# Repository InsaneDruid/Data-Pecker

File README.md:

# The Data Pecker - a DB High-Res clone
The Data Pecker is a 100% compatible clone of the DB High-Res graphics board for PET/CBM 8000 series computers from 1982.
It implements all the features, with the option to build a 62256-based RAM-board instead of the original one using eight 6116.
Most of the components are readily available. Chips not available from Mouser or Digikey can still be purchased from a variety of sources in China. 

[Schematic](https://github.com/InsaneDruid/Data-Pecker/blob/main/dph_mainboard/dph_mainboard.pdf "Schematic")  

[Bill of Materials](https://htmlpreview.github.io/?https://github.com/InsaneDruid/Data-Pecker/blob/main/dph_mainboard/bom/dph_mainboard_bom.html "Bill of Materials")

[Wire connections](https://github.com/InsaneDruid/Data-Pecker/blob/main/dph_mainboard/dph_mainboard_connections.pdf "Wire connections" )
## The original RAM Board
The is the true-to-the-original version of the RAM board containing eight 6116 SRAM ICs.

[Schematic](https://github.com/InsaneDruid/Data-Pecker/blob/main/dph_ram/dph_ram.pdf "Schematic")  

[Bill of Materials](https://htmlpreview.github.io/?https://github.com/InsaneDruid/Data-Pecker/blob/main/dph_ram/bom/dph_ram_bom.html "Bill of Materials")

## The simplified RAM Board
This version replaces the old SRAM chips with a more modern 62256.

[Schematic](https://github.com/InsaneDruid/Data-Pecker/blob/main/dph_ram_optimized/dph_ram_optimized.pdf "Schematic")  

[Bill of Materials](https://htmlpreview.github.io/?https://github.com/InsaneDruid/Data-Pecker/blob/main/dph_ram_optimized/bom/dph_ram_optimized_bom.html "Bill of Materials")

## The Firmware
There are several ways to get both the programmed 2332A	ROM and TBP18s030 PROM	
chips for the Low Speed Graphik. One is to use U29 and U11 from a original HSG. 
This works well and is especially interesting for those seeking to replace a broken original HSG pcb.

The other possibility is to program a 2532 EPROM replacing U29 and a 18S030 PROM (or compatible, like 82S123, 27S19, 6331, 74S288, 7603a)
replacing U11. The firmware needed for flashing can be found on the web. The 18S030 can also be replaced by a GAL.

## The License
This work is licensed under a Creative Commons Attribution-ShareAlike 4.0 International License.  
See https://creativecommons.org/licenses/by-sa/4.0/.

## The Credits
This work would not have been possible without the help from a bunch of amazing people from [VzEkC e. V. forums](https://forum.classic-computing.de/forum/ "forum.classic-computing.de"). Many thanks go out to:

* *Toast_r* - for providing reference images and ohming out the hidden traces

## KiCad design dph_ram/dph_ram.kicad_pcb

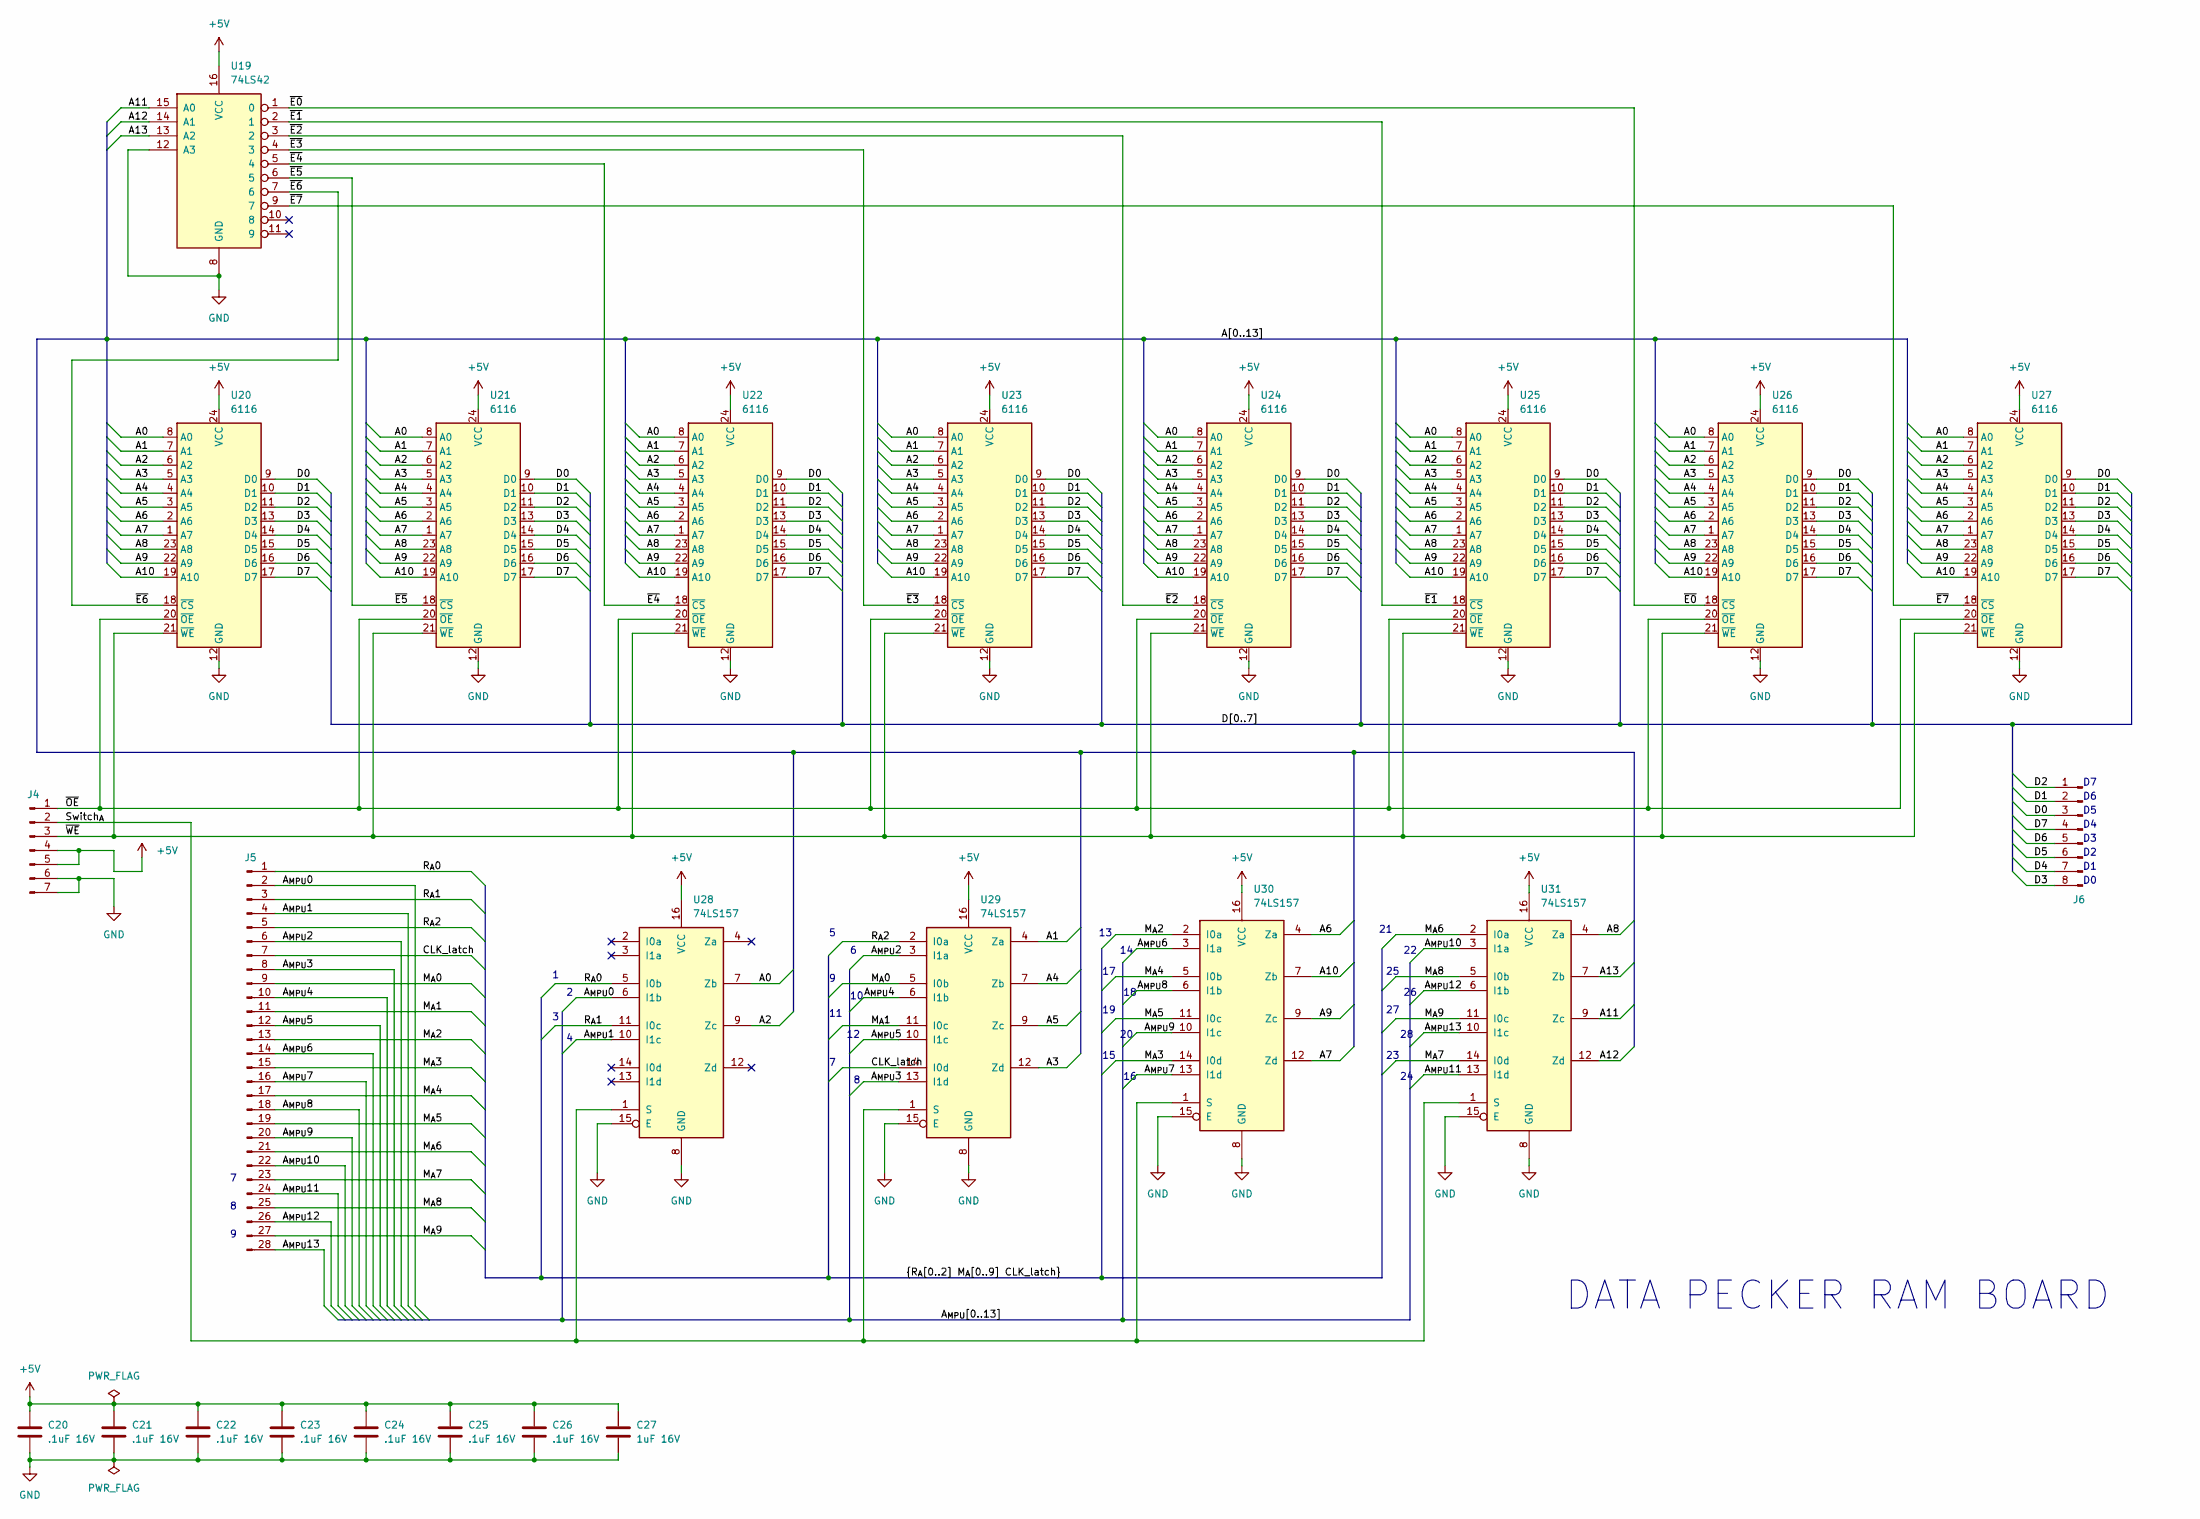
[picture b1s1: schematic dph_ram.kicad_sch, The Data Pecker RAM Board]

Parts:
C20, C21, C22, C23, C24, C25, C26: .1uF 16V; C_Disc_D3.0mm_W1.6mm_P2.50mm
C27: 1uF 16V; C_Disc_D4.3mm_W1.9mm_P5.08mm
J4: Conn_01x07_Pin; PinHeader_1x07_P2.54mm_Vertical
J5: Conn_01x28_Pin; PinHeader_1x28_P2.54mm_Vertical
J6: Conn_01x08_Pin; PinHeader_1x08_P2.54mm_Vertical
U19: 74LS42; DIP-16_W7.62mm_LongPads
U20, U21, U22, U23, U24, U25, U26, U27: 6116; DIP-24_W15.24mm_LongPads
U28, U29, U30, U31: 74LS157; DIP-16_W7.62mm_LongPads

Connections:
+5V: C20.1, C21.1, C22.1, C23.1, C24.1, C25.1, C26.1, C27.1, J4.4, J4.5, U19.16 (VCC), U20.24 (VCC), U21.24 (VCC), U22.24 (VCC), U23.24 (VCC), U24.24 (VCC), U25.24 (VCC), U26.24 (VCC), U27.24 (VCC), U28.16 (VCC), U29.16 (VCC), U30.16 (VCC), U31.16 (VCC)
/A0: U20.8 (A0), U21.8 (A0), U22.8 (A0), U23.8 (A0), U24.8 (A0), U25.8 (A0), U26.8 (A0), U27.8 (A0), U28.7 (Zb)
/A1: U20.7 (A1), U21.7 (A1), U22.7 (A1), U23.7 (A1), U24.7 (A1), U25.7 (A1), U26.7 (A1), U27.7 (A1), U29.4 (Za)
/A2: U20.6 (A2), U21.6 (A2), U22.6 (A2), U23.6 (A2), U24.6 (A2), U25.6 (A2), U26.6 (A2), U27.6 (A2), U28.9 (Zc)
/A3: U20.5 (A3), U21.5 (A3), U22.5 (A3), U23.5 (A3), U24.5 (A3), U25.5 (A3), U26.5 (A3), U27.5 (A3), U29.12 (Zd)
/A4: U20.4 (A4), U21.4 (A4), U22.4 (A4), U23.4 (A4), U24.4 (A4), U25.4 (A4), U26.4 (A4), U27.4 (A4), U29.7 (Zb)
/A5: U20.3 (A5), U21.3 (A5), U22.3 (A5), U23.3 (A5), U24.3 (A5), U25.3 (A5), U26.3 (A5), U27.3 (A5), U29.9 (Zc)
/A6: U20.2 (A6), U21.2 (A6), U22.2 (A6), U23.2 (A6), U24.2 (A6), U25.2 (A6), U26.2 (A6), U27.2 (A6), U30.4 (Za)
/A7: U20.1 (A7), U21.1 (A7), U22.1 (A7), U23.1 (A7), U24.1 (A7), U25.1 (A7), U26.1 (A7), U27.1 (A7), U30.12 (Zd)
/A8: U20.23 (A8), U21.23 (A8), U22.23 (A8), U23.23 (A8), U24.23 (A8), U25.23 (A8), U26.23 (A8), U27.23 (A8), U31.4 (Za)
/A9: U20.22 (A9), U21.22 (A9), U22.22 (A9), U23.22 (A9), U24.22 (A9), U25.22 (A9), U26.22 (A9), U27.22 (A9), U30.9 (Zc)
/A10: U20.19 (A10), U21.19 (A10), U22.19 (A10), U23.19 (A10), U24.19 (A10), U25.19 (A10), U26.19 (A10), U27.19 (A10), U30.7 (Zb)
/A11: U19.15 (A0), U31.9 (Zc)
/A12: U19.14 (A1), U31.12 (Zd)
/A13: U19.13 (A2), U31.7 (Zb)
/A_{MPU}0: J5.2, U28.6 (I1b)
/A_{MPU}1: J5.4, U28.10 (I1c)
/A_{MPU}2: J5.6, U29.3 (I1a)
/A_{MPU}3: J5.8, U29.13 (I1d)
/A_{MPU}4: J5.10, U29.6 (I1b)
/A_{MPU}5: J5.12, U29.10 (I1c)
/A_{MPU}6: J5.14, U30.3 (I1a)
/A_{MPU}7: J5.16, U30.13 (I1d)
/A_{MPU}8: J5.18, U30.6 (I1b)
/A_{MPU}9: J5.20, U30.10 (I1c)
/A_{MPU}10: J5.22, U31.3 (I1a)
/A_{MPU}11: J5.24, U31.13 (I1d)
/A_{MPU}12: J5.26, U31.6 (I1b)
/A_{MPU}13: J5.28, U31.10 (I1c)
/CLK_latch: J5.7, U29.14 (I0d)
/D0: J6.3, U20.9 (D0), U21.9 (D0), U22.9 (D0), U23.9 (D0), U24.9 (D0), U25.9 (D0), U26.9 (D0), U27.9 (D0)
/D1: J6.2, U20.10 (D1), U21.10 (D1), U22.10 (D1), U23.10 (D1), U24.10 (D1), U25.10 (D1), U26.10 (D1), U27.10 (D1)
/D2: J6.1, U20.11 (D2), U21.11 (D2), U22.11 (D2), U23.11 (D2), U24.11 (D2), U25.11 (D2), U26.11 (D2), U27.11 (D2)
/D3: J6.8, U20.13 (D3), U21.13 (D3), U22.13 (D3), U23.13 (D3), U24.13 (D3), U25.13 (D3), U26.13 (D3), U27.13 (D3)
/D4: J6.7, U20.14 (D4), U21.14 (D4), U22.14 (D4), U23.14 (D4), U24.14 (D4), U25.14 (D4), U26.14 (D4), U27.14 (D4)
/D5: J6.6, U20.15 (D5), U21.15 (D5), U22.15 (D5), U23.15 (D5), U24.15 (D5), U25.15 (D5), U26.15 (D5), U27.15 (D5)
/D6: J6.5, U20.16 (D6), U21.16 (D6), U22.16 (D6), U23.16 (D6), U24.16 (D6), U25.16 (D6), U26.16 (D6), U27.16 (D6)
/D7: J6.4, U20.17 (D7), U21.17 (D7), U22.17 (D7), U23.17 (D7), U24.17 (D7), U25.17 (D7), U26.17 (D7), U27.17 (D7)
/M_{A}0: J5.9, U29.5 (I0b)
/M_{A}1: J5.11, U29.11 (I0c)
/M_{A}2: J5.13, U30.2 (I0a)
/M_{A}3: J5.15, U30.14 (I0d)
/M_{A}4: J5.17, U30.5 (I0b)
/M_{A}5: J5.19, U30.11 (I0c)
/M_{A}6: J5.21, U31.2 (I0a)
/M_{A}7: J5.23, U31.14 (I0d)
/M_{A}8: J5.25, U31.5 (I0b)
/M_{A}9: J5.27, U31.11 (I0c)
/R_{A}0: J5.1, U28.5 (I0b)
/R_{A}1: J5.3, U28.11 (I0c)
/R_{A}2: J5.5, U29.2 (I0a)
/Switch_{A}: J4.2, U28.1 (S), U29.1 (S), U30.1 (S), U31.1 (S)
/~E0: U19.1 (0), U26.18 (~CS)
/~E1: U19.2 (1), U25.18 (~CS)
/~E2: U19.3 (2), U24.18 (~CS)
/~E3: U19.4 (3), U23.18 (~CS)
/~E4: U19.5 (4), U22.18 (~CS)
/~E5: U19.6 (5), U21.18 (~CS)
/~E6: U19.7 (6), U20.18 (~CS)
/~E7: U19.9 (7), U27.18 (~CS)
/~OE: J4.1, U20.20 (~OE), U21.20 (~OE), U22.20 (~OE), U23.20 (~OE), U24.20 (~OE), U25.20 (~OE), U26.20 (~OE), U27.20 (~OE)
/~WE: J4.3, U20.21 (~WE), U21.21 (~WE), U22.21 (~WE), U23.21 (~WE), U24.21 (~WE), U25.21 (~WE), U26.21 (~WE), U27.21 (~WE)
GND: C20.2, C21.2, C22.2, C23.2, C24.2, C25.2, C26.2, C27.2, J4.6, J4.7, U19.8 (GND), U19.12 (A3), U20.12 (GND), U21.12 (GND), U22.12 (GND), U23.12 (GND), U24.12 (GND), U25.12 (GND), U26.12 (GND), U27.12 (GND), U28.8 (GND), U28.15 (E), U29.8 (GND), U29.15 (E), U30.8 (GND), U30.15 (E), U31.8 (GND), U31.15 (E)

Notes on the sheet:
DATA PECKER RAM BOARD

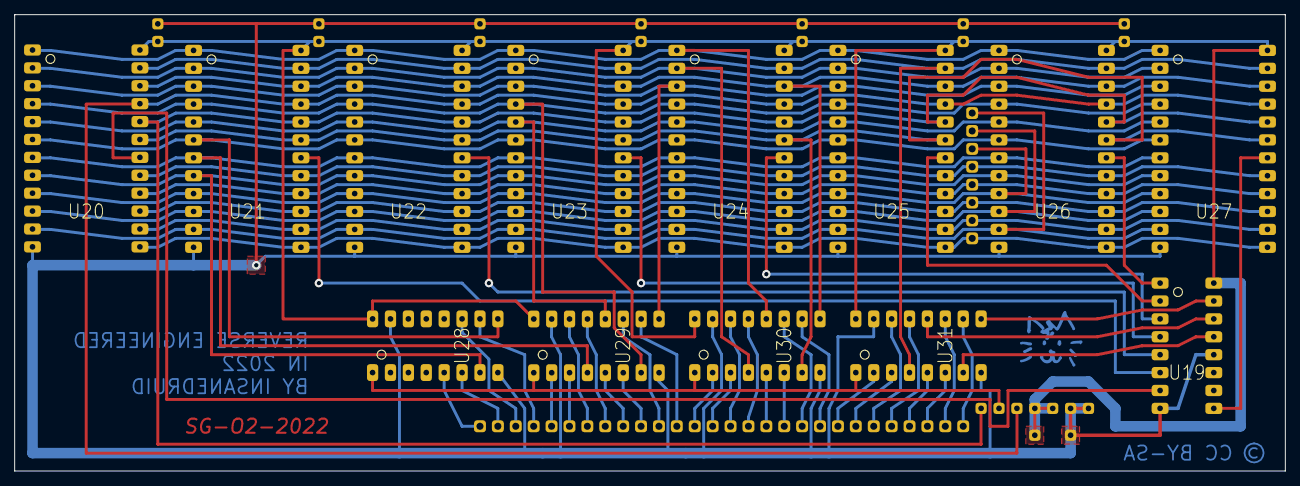
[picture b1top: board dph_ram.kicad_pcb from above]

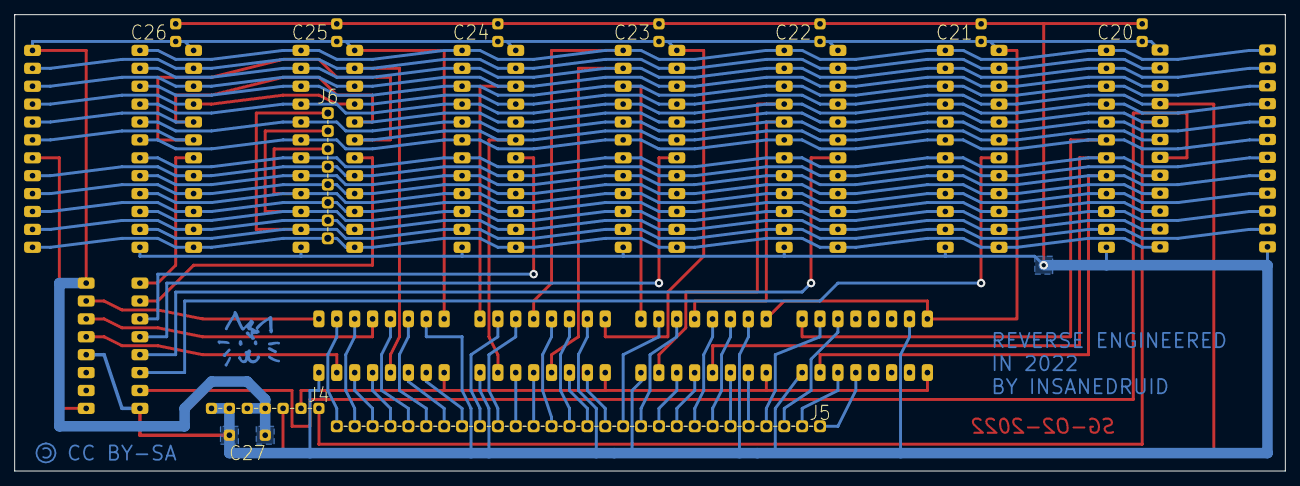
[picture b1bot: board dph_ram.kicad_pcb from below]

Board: 2 copper layers, 180.3 x 64.8 mm, 24 parts (3 on the bottom side), 63 nets.

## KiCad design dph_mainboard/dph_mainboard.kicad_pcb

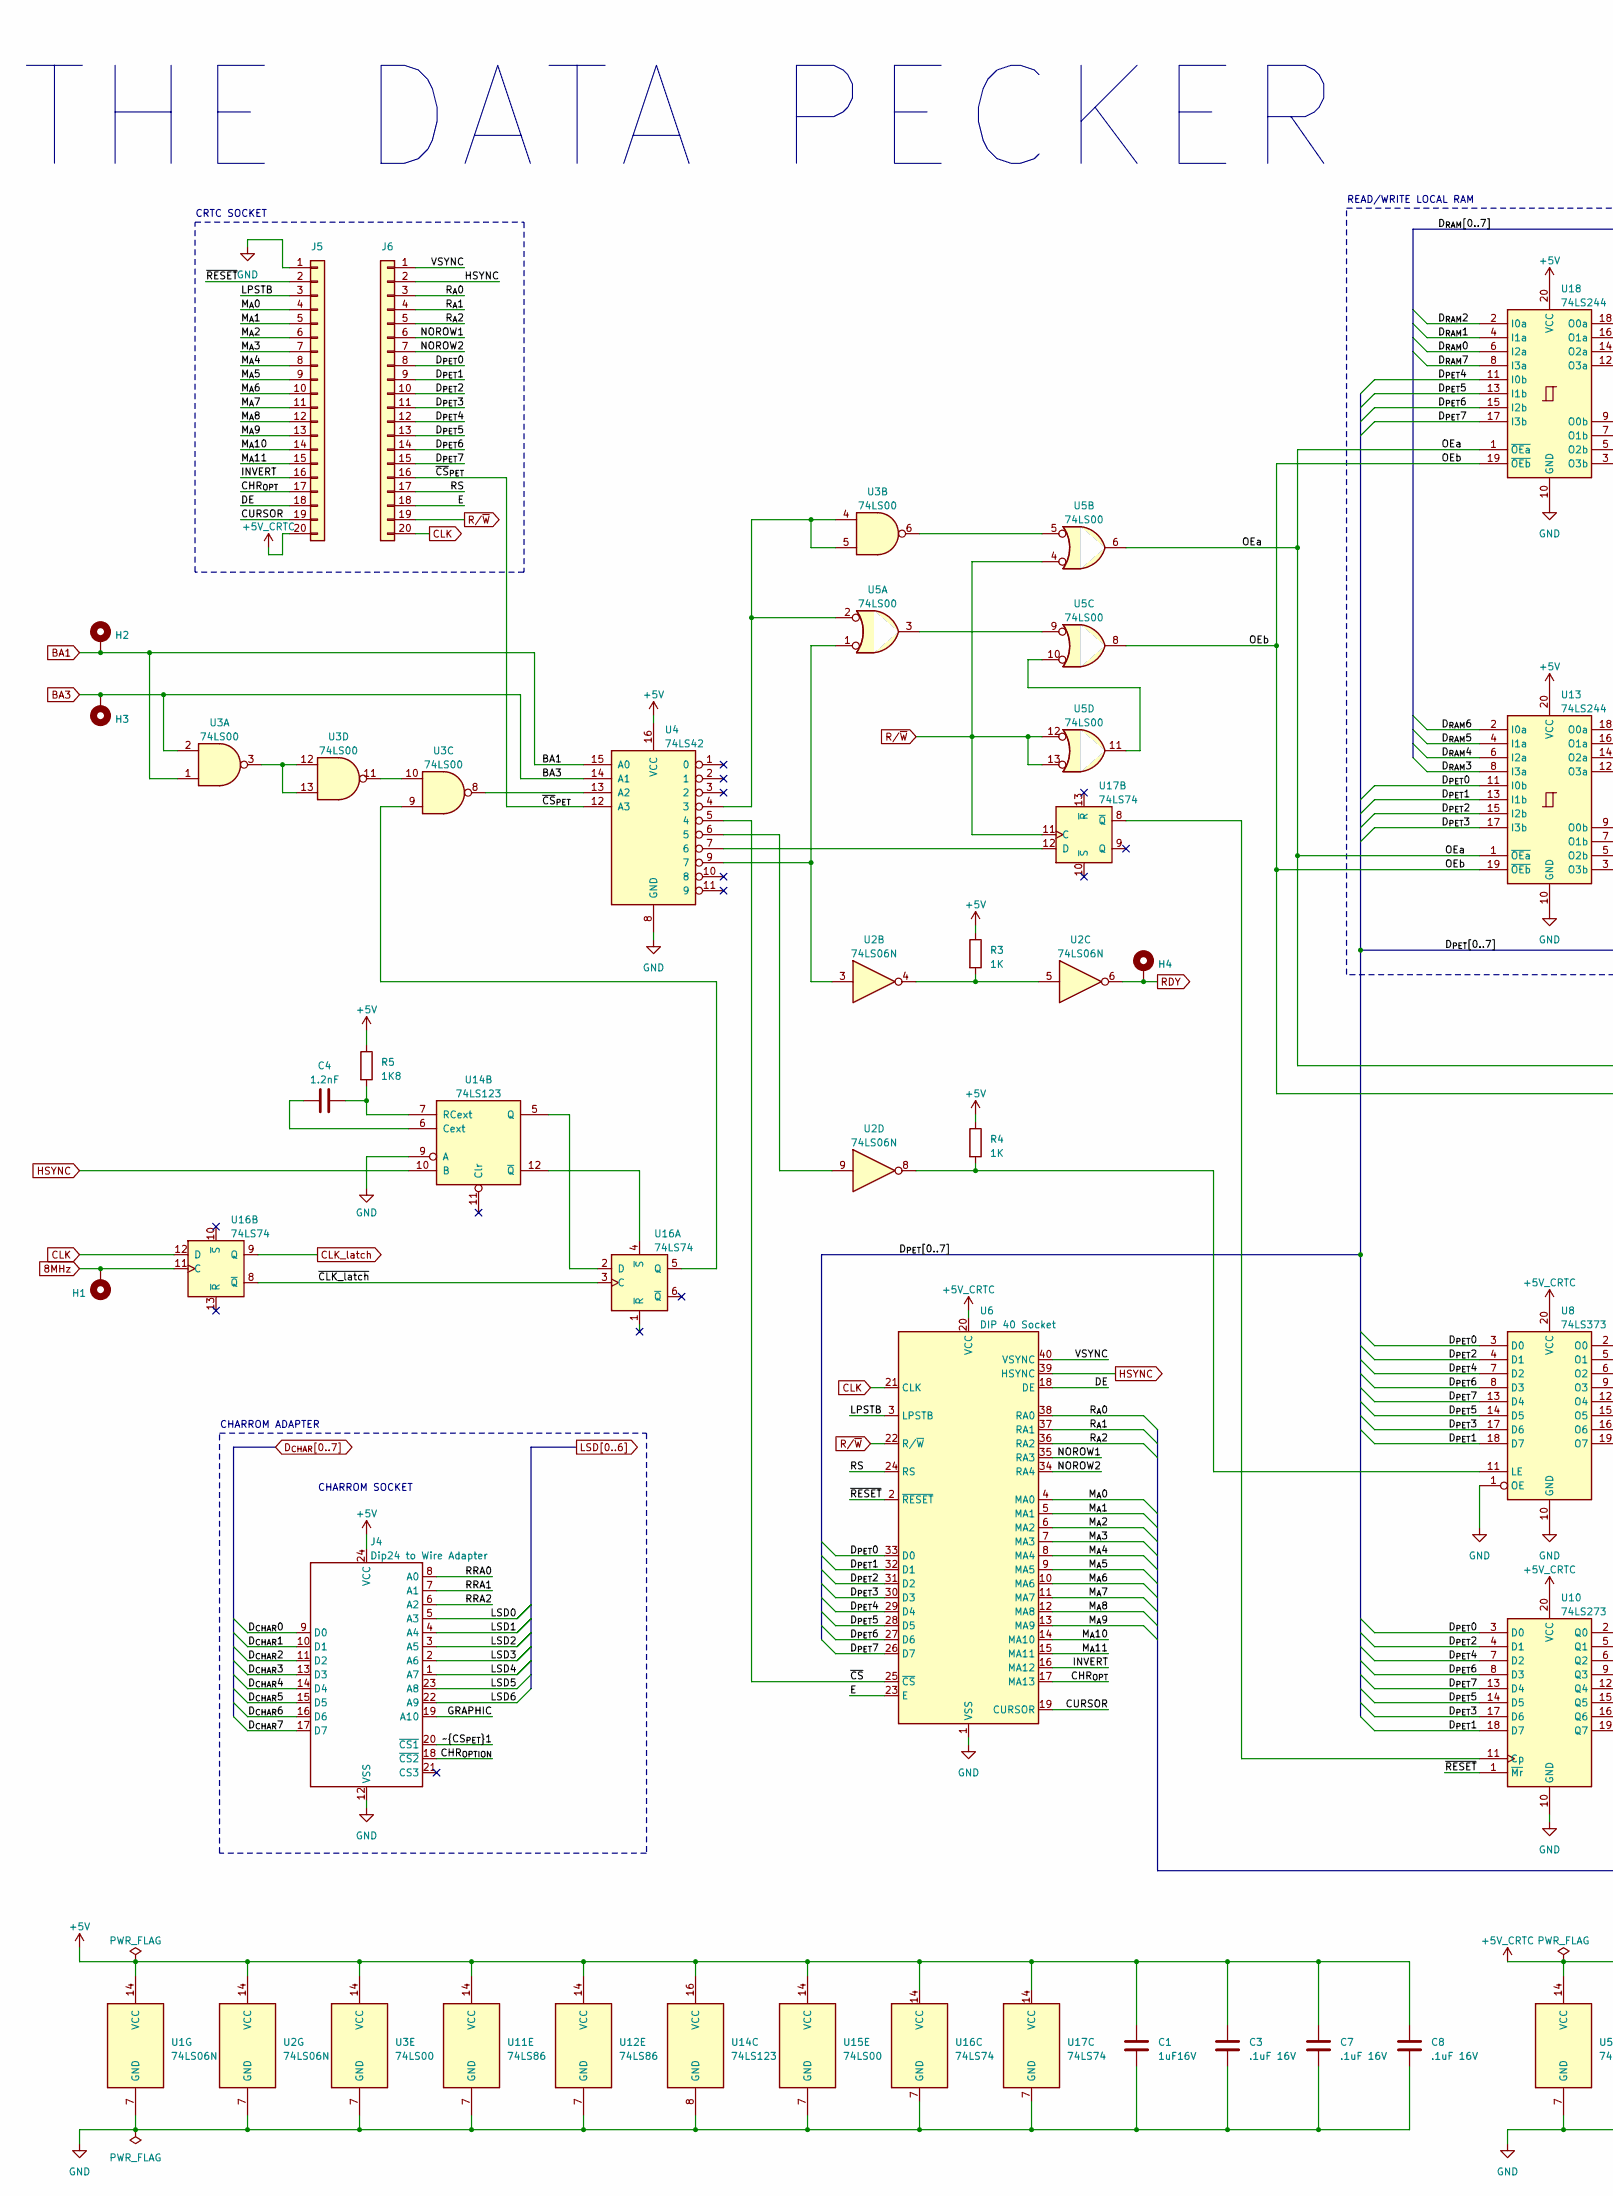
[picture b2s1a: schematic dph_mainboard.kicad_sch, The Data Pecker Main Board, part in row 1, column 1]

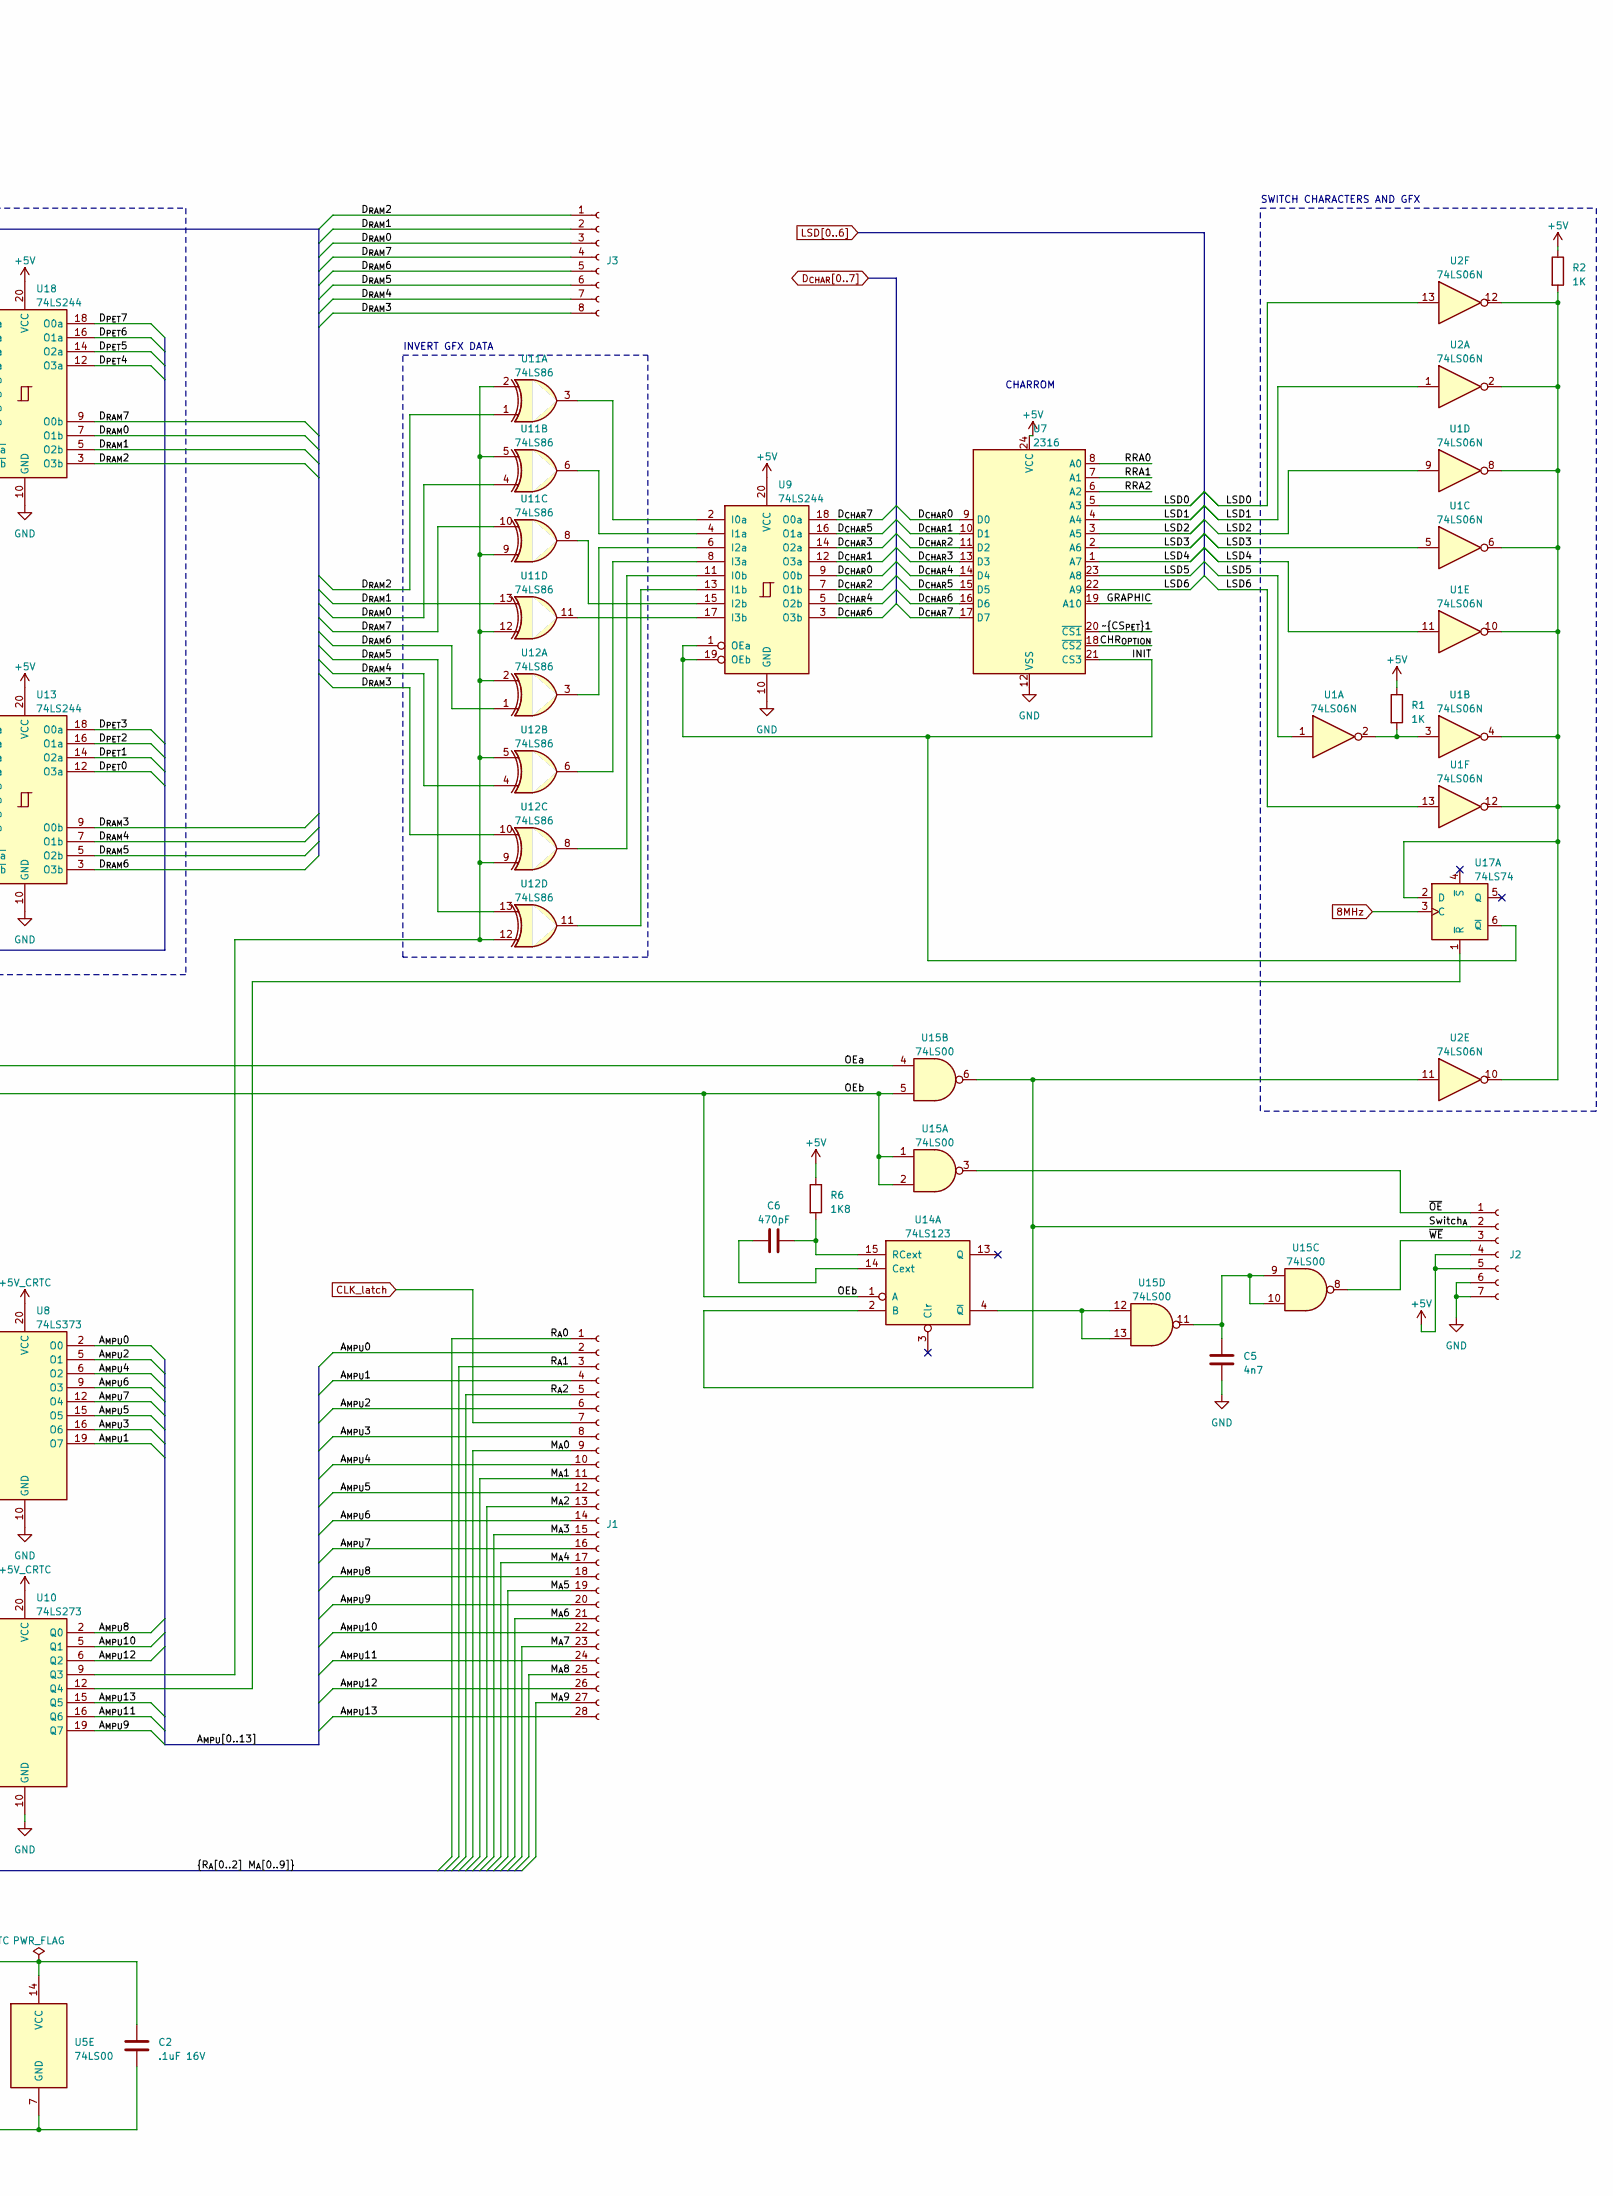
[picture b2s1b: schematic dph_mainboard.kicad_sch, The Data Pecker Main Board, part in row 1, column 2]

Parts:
C1: 1uF16V; C_Disc_D4.3mm_W1.9mm_P5.08mm
C2, C3, C7, C8: .1uF 16V; C_Disc_D4.3mm_W1.9mm_P5.08mm
C4: 1.2nF; C_Disc_D3.0mm_W1.6mm_P2.50mm
C5: 4n7; C_Disc_D4.3mm_W1.9mm_P5.08mm
C6: 470pF; C_Disc_D3.0mm_W1.6mm_P2.50mm
H1, H2, H3, H4: MountingHole_Pad; SolderWire-0.15sqmm_1x01_D0.5mm_OD1.5mm
J1: Conn_01x28_Socket; PinSocket_1x28_P2.54mm_Vertical
J2: Conn_01x7_Socket; PinSocket_1x07_P2.54mm_Vertical
J3: Conn_01x8_Socket; PinSocket_1x08_P2.54mm_Vertical
J4: Dip24 to Wire Adapter; DIP-24_W15.24mm_WireAdapter
J5, J6: Conn_01x20_Pin; PinHeader_1x20_P2.54mm_Vertical
R1, R2, R3, R4: 1K; R_Axial_DIN0207_L6.3mm_D2.5mm_P10.16mm_Horizontal
R5, R6: 1K8; R_Axial_DIN0204_L3.6mm_D1.6mm_P7.62mm_Horizontal
U1, U2: 74LS06N; DIP-14_W7.62mm_LongPads
U3, U5, U15: 74LS00; DIP-14_W7.62mm_LongPads
U4: 74LS42; DIP-16_W7.62mm_LongPads
U6: DIP 40 Socket; DIP-40_W15.24mm_Socket_LongPads
U7: 2316; DIP-24_W15.24mm_Socket_LongPads
U8: 74LS373; DIP-20_W7.62mm_LongPads
U9, U13, U18: 74LS244; DIP-20_W7.62mm_LongPads
U10: 74LS273; DIP-20_W7.62mm_LongPads
U11, U12: 74LS86; DIP-14_W7.62mm_LongPads
U14: 74LS123; DIP-16_W7.62mm_LongPads
U16, U17: 74LS74; DIP-14_W7.62mm_LongPads

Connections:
8MHz: H1.1, U16.11 (C), U17.3 (C)
+5V: C1.1, C3.1, C7.1, C8.1, J2.4, J2.5, J4.24 (VCC), R1.1, R2.1, R3.1, R4.1, R5.1, R6.1, U1.14 (VCC), U2.14 (VCC), U3.14 (VCC), U4.16 (VCC), U7.24 (VCC), U9.20 (VCC), U11.14 (VCC), U12.14 (VCC), U13.20 (VCC), U14.16 (VCC), U15.14 (VCC), U16.14 (VCC), U17.14 (VCC), U18.20 (VCC)
+5V_CRTC: C2.1, J5.20, U5.14 (VCC), U6.20 (VCC), U8.20 (VCC), U10.20 (VCC)
/A_{MPU}0: J1.2, U8.2 (O0)
/A_{MPU}1: J1.4, U8.19 (O7)
/A_{MPU}2: J1.6, U8.5 (O1)
/A_{MPU}3: J1.8, U8.16 (O6)
/A_{MPU}4: J1.10, U8.6 (O2)
/A_{MPU}5: J1.12, U8.15 (O5)
/A_{MPU}6: J1.14, U8.9 (O3)
/A_{MPU}7: J1.16, U8.12 (O4)
/A_{MPU}8: J1.18, U10.2 (Q0)
/A_{MPU}9: J1.20, U10.19 (Q7)
/A_{MPU}10: J1.22, U10.5 (Q1)
/A_{MPU}11: J1.24, U10.16 (Q6)
/A_{MPU}12: J1.26, U10.6 (Q2)
/A_{MPU}13: J1.28, U10.15 (Q5)
/CHR_{OPTION}: J4.18 (~CS2), U7.18 (~CS2)
/CHR_{OPT}: J5.17, U6.17 (MA13)
/CURSOR: J5.19, U6.19 (CURSOR)
/DE: J5.18, U6.18 (DE)
/D_{PET}0: J6.8, U6.33 (D0), U8.3 (D0), U10.3 (D0), U13.11 (I0b), U13.12 (O3a)
/D_{PET}1: J6.9, U6.32 (D1), U8.18 (D7), U10.18 (D7), U13.13 (I1b), U13.14 (O2a)
/D_{PET}2: J6.10, U6.31 (D2), U8.4 (D1), U10.4 (D1), U13.15 (I2b), U13.16 (O1a)
/D_{PET}3: J6.11, U6.30 (D3), U8.17 (D6), U10.17 (D6), U13.17 (I3b), U13.18 (O0a)
/D_{PET}4: J6.12, U6.29 (D4), U8.7 (D2), U10.7 (D2), U18.11 (I0b), U18.12 (O3a)
/D_{PET}5: J6.13, U6.28 (D5), U8.14 (D5), U10.14 (D5), U18.13 (I1b), U18.14 (O2a)
/D_{PET}6: J6.14, U6.27 (D6), U8.8 (D3), U10.8 (D3), U18.15 (I2b), U18.16 (O1a)
/D_{PET}7: J6.15, U6.26 (D7), U8.13 (D4), U10.13 (D4), U18.17 (I3b), U18.18 (O0a)
/D_{RAM}0: J3.3, U11.4, U18.6 (I2a), U18.7 (O1b)
/D_{RAM}1: J3.2, U11.13, U18.4 (I1a), U18.5 (O2b)
/D_{RAM}2: J3.1, U11.1, U18.2 (I0a), U18.3 (O3b)
/D_{RAM}3: J3.8, U12.10, U13.8 (I3a), U13.9 (O0b)
/D_{RAM}4: J3.7, U12.4, U13.6 (I2a), U13.7 (O1b)
/D_{RAM}5: J3.6, U12.13, U13.4 (I1a), U13.5 (O2b)
/D_{RAM}6: J3.5, U12.1, U13.2 (I0a), U13.3 (O3b)
/D_{RAM}7: J3.4, U11.10, U18.8 (I3a), U18.9 (O0b)
/E: J6.18, U6.23 (E)
/GRAPHIC: J4.19 (A10), U7.19 (A10)
/INIT: U7.21 (CS3), U9.1 (OEa), U9.19 (OEb), U17.6 (~Q)
/INVERT: J5.16, U6.16 (MA12)
/LPSTB: J5.3, U6.3 (LPSTB)
/M_{A}0: J1.9, J5.4, U6.4 (MA0)
/M_{A}1: J1.11, J5.5, U6.5 (MA1)
/M_{A}2: J1.13, J5.6, U6.6 (MA2)
/M_{A}3: J1.15, J5.7, U6.7 (MA3)
/M_{A}4: J1.17, J5.8, U6.8 (MA4)
/M_{A}5: J1.19, J5.9, U6.9 (MA5)
/M_{A}6: J1.21, J5.10, U6.10 (MA6)
/M_{A}7: J1.23, J5.11, U6.11 (MA7)
/M_{A}8: J1.25, J5.12, U6.12 (MA8)
/M_{A}9: J1.27, J5.13, U6.13 (MA9)
/M_{A}10: J5.14, U6.14 (MA10)
/M_{A}11: J5.15, U6.15 (MA11)
/NOROW1: J6.6, U6.35 (RA3)
/NOROW2: J6.7, U6.34 (RA4)
/OEa: U5.6, U13.1 (~OEa), U15.4, U18.1 (~OEa)
/OEb: U5.8, U13.19 (~OEb), U14.1 (A), U15.1, U15.2, U15.5, U18.19 (~OEb)
/RRA0: J4.8 (A0), U7.8 (A0)
/RRA1: J4.7 (A1), U7.7 (A1)
/RRA2: J4.6 (A2), U7.6 (A2)
/RS: J6.17, U6.24 (RS)
/R_{A}0: J1.1, J6.3, U6.38 (RA0)
/R_{A}1: J1.3, J6.4, U6.37 (RA1)
/R_{A}2: J1.5, J6.5, U6.36 (RA2)
/Switch_{A}: J2.2, U2.11, U14.2 (B), U15.6
/VSYNC: J6.1, U6.40 (VSYNC)
/~CLK_latch: U16.3 (C), U16.8 (~Q)
/~CS_{PET}1: J4.20 (~CS1), U7.20 (~CS1)
/~CS: U4.5 (4), U6.25 (~CS)
/~CS_{PET}: J6.16, U4.12 (A3)
/~OE: J2.1, U15.3
/~RESET: J5.2, U6.2 (~RESET), U10.1 (~Mr)
/~WE: J2.3, U15.8
BA1: H2.1, U3.1, U4.15 (A0)
BA3: H3.1, U3.2, U4.14 (A1)
CLK: J6.20, U6.21 (CLK), U16.12 (D)
CLK_latch: J1.7, U16.9 (Q)
D_{CHAR}0: J4.9 (D0), U7.9 (D0), U9.9 (O0b)
D_{CHAR}1: J4.10 (D1), U7.10 (D1), U9.12 (O3a)
D_{CHAR}2: J4.11 (D2), U7.11 (D2), U9.7 (O1b)
D_{CHAR}3: J4.13 (D3), U7.13 (D3), U9.14 (O2a)
D_{CHAR}4: J4.14 (D4), U7.14 (D4), U9.5 (O2b)
D_{CHAR}5: J4.15 (D5), U7.15 (D5), U9.16 (O1a)
D_{CHAR}6: J4.16 (D6), U7.16 (D6), U9.3 (O3b)
D_{CHAR}7: J4.17 (D7), U7.17 (D7), U9.18 (O0a)
GND: C1.2, C2.2, C3.2, C5.2, C7.2, C8.2, J2.6, J2.7, J4.12 (VSS), J5.1, U1.7 (GND), U2.7 (GND), U3.7 (GND), U4.8 (GND), U5.7 (GND), U6.1 (VSS), U7.12 (VSS), U8.1 (OE), U8.10 (GND), U9.10 (GND), U10.10 (GND), U11.7 (GND), U12.7 (GND), U13.10 (GND), U14.8 (GND), U14.9 (A), U15.7 (GND), U16.7 (GND), U17.7 (GND), U18.10 (GND)
HSYNC: J6.2, U6.39 (HSYNC), U14.10 (B)
LSD0: J4.5 (A3), U2.13, U7.5 (A3)
LSD1: J4.4 (A4), U2.1, U7.4 (A4)
LSD2: J4.3 (A5), U1.9, U7.3 (A5)
LSD3: J4.2 (A6), U1.5, U7.2 (A6)
LSD4: J4.1 (A7), U1.11, U7.1 (A7)
LSD5: J4.23 (A8), U1.1, U7.23 (A8)
LSD6: J4.22 (A9), U1.13, U7.22 (A9)
unnamed: C5.1, U15.9, U15.10, U15.11
unnamed: R1.2, U1.2, U1.3
unnamed: R3.2, U2.4, U2.5
unnamed: U3.6, U5.5
unnamed: U3.10, U3.11
unnamed: U3.3, U3.12, U3.13
unnamed: U3.4, U3.5, U4.4 (3), U5.2
unnamed: U2.9, U4.6 (5)
unnamed: U2.3, U4.9 (7), U5.1
unnamed: U3.8, U4.13 (A2)
unnamed: U5.3, U5.9
unnamed: U5.10, U5.11
unnamed: R4.2, U2.8, U8.11 (LE)
unnamed: U9.2 (I0a), U11.3
unnamed: U9.11 (I0b), U12.8
unnamed: U9.4 (I1a), U11.6
unnamed: U9.13 (I1b), U12.11
unnamed: U9.6 (I2a), U12.3
unnamed: U9.15 (I2b), U11.8
unnamed: U9.8 (I3a), U12.6
unnamed: U9.17 (I3b), U11.11
unnamed: U10.11 (Cp), U17.8 (~Q)
unnamed: U10.9 (Q3), U11.2, U11.5, U11.9, U11.12, U12.2, U12.5, U12.9, U12.12
unnamed: U10.12 (Q4), U17.1 (~R)
unnamed: C6.1, U14.14 (Cext)
unnamed: C6.2, R6.2, U14.15 (RCext)
unnamed: U14.4 (~Q), U15.12, U15.13
unnamed: C4.1, U14.6 (Cext)
unnamed: U14.5 (Q), U16.2 (D)
unnamed: C4.2, R5.2, U14.7 (RCext)
unnamed: U14.12 (~Q), U16.4 (~S)
unnamed: U3.9, U16.5 (Q)
unnamed: R2.2, U1.4, U1.6, U1.8, U1.10, U1.12, U2.2, U2.10, U2.12, U17.2 (D)
unnamed: U4.7 (6), U17.12 (D)
RDY: H4.1, U2.6
R/~W: J6.19, U5.4, U5.12, U5.13, U6.22 (R/~W), U17.11 (C)

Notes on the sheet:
THE DATA PECKER
CRTC SOCKET
CHARROM SOCKET
READ/WRITE LOCAL RAM
CHARROM ADAPTER
SWITCH CHARACTERS AND GFX
CHARROM
INVERT GFX DATA

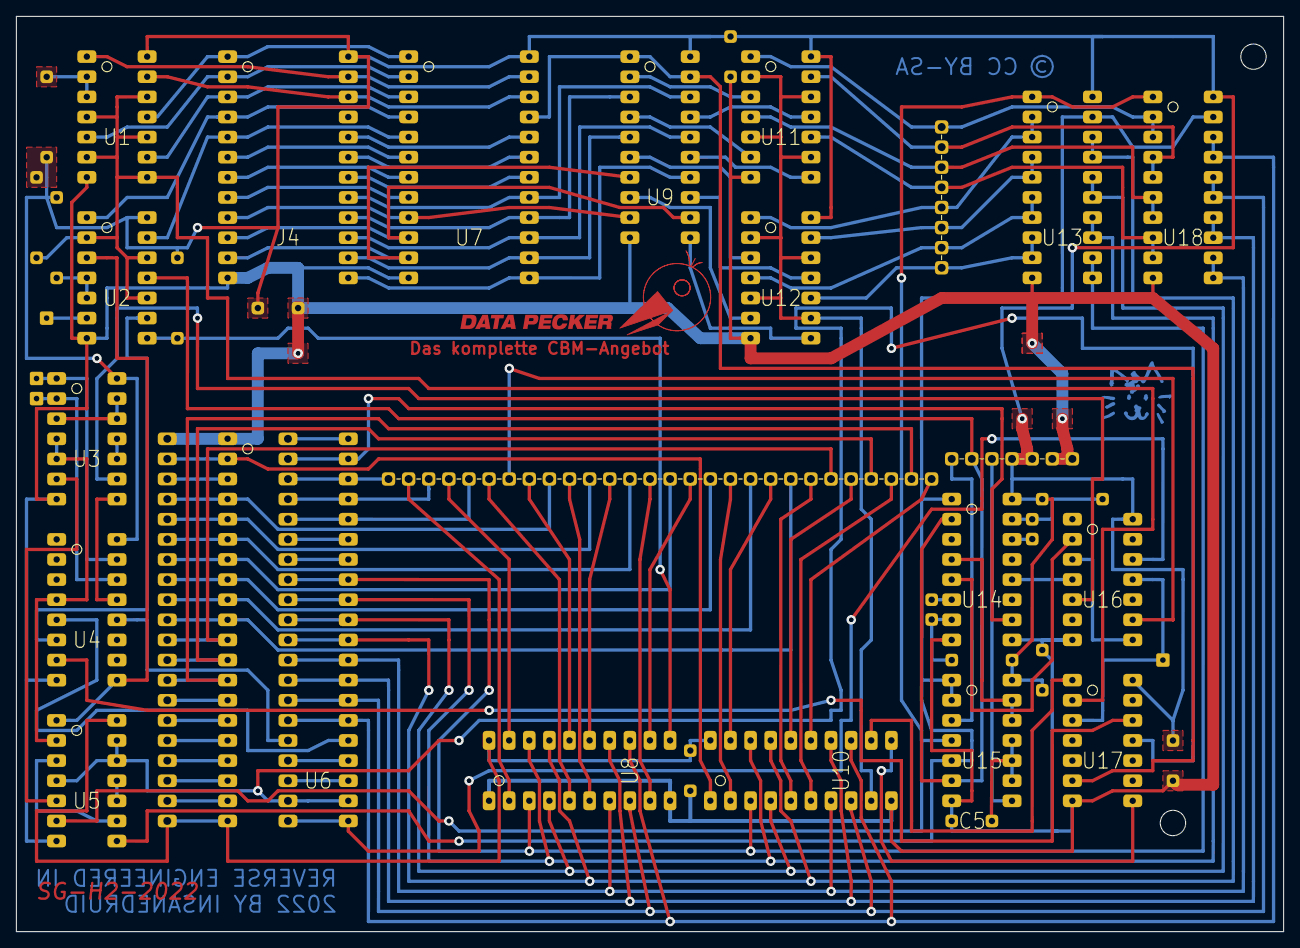
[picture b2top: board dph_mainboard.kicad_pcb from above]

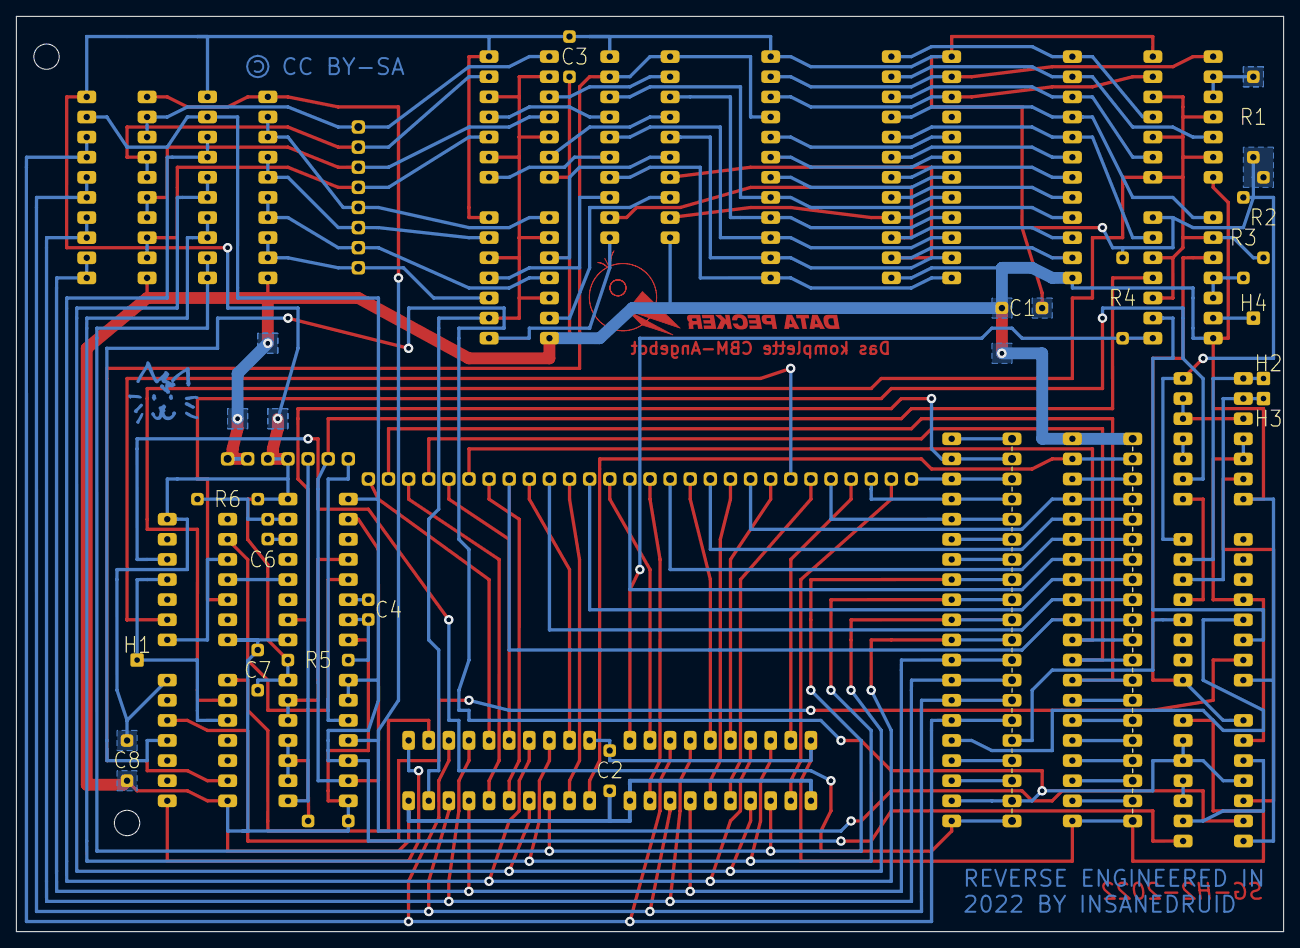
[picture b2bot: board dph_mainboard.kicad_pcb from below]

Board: 2 copper layers, 160.0 x 115.6 mm, 42 parts (2 on the bottom side), 131 nets.

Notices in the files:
dph_mainboard/dph_mainboard.kicad_pcb:
License: CC BY-SA 4.0
CC BY-SA
